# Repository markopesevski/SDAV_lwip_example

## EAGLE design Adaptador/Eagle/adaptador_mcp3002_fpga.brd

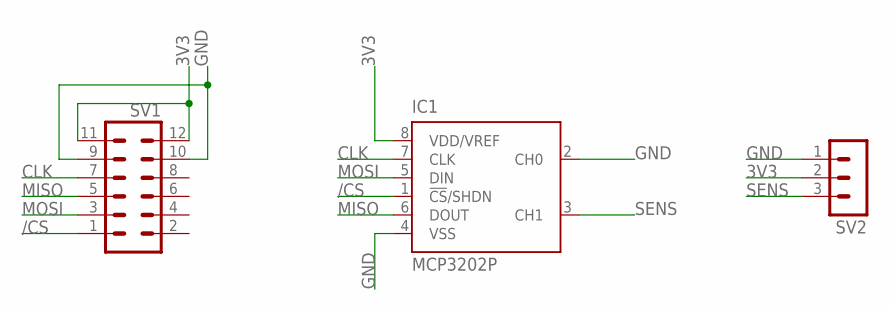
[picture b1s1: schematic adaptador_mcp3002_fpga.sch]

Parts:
IC1: MCP3202P; DIL8
SV1: MA06-2
SV2: MA03-1

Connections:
3V3: IC1.8 (VDD/VREF), SV1.11, SV1.12, SV2.2
/CS: IC1.1 (!CS!/SHDN), SV1.1
CLK: IC1.7 (CLK), SV1.7
GND: IC1.2 (CH0), IC1.4 (VSS), SV1.9, SV1.10, SV2.1
MISO: IC1.6 (DOUT), SV1.5
MOSI: IC1.5 (DIN), SV1.3
SENS: IC1.3 (CH1), SV2.3

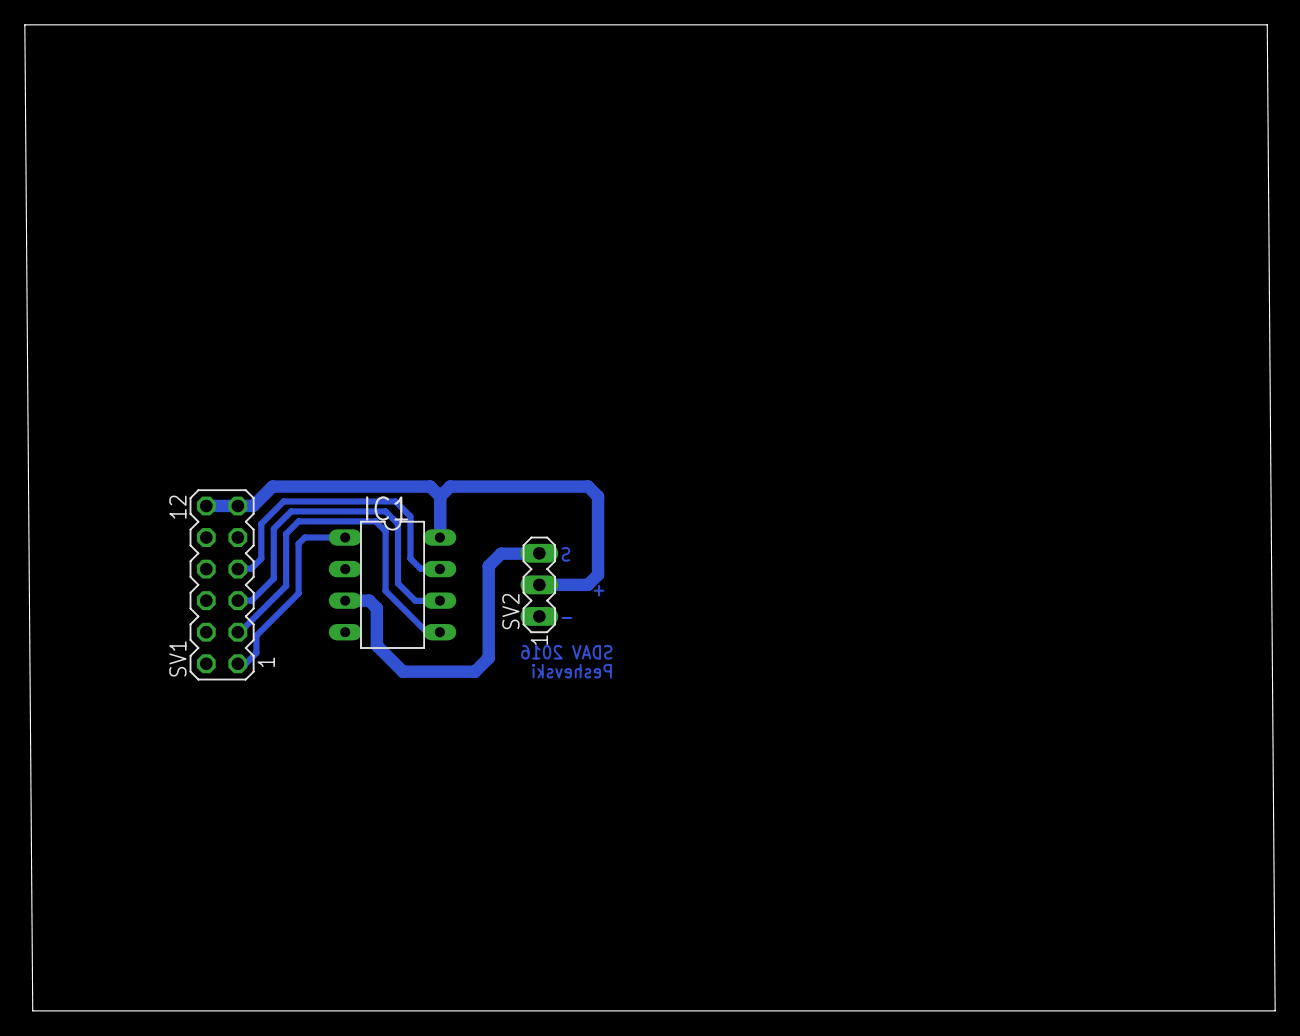
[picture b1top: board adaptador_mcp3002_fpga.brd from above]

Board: 2 copper layers, 100.6 x 79.4 mm, 3 parts (0 on the bottom side), 7 nets.

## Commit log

2016-10-20 Commit inicial de l'exemple de LWIP de Xilinx, sense haver fet cap modificacio
2016-10-20 Afegit README.md
2016-10-24 Primer canvi cap a la web propia
2016-10-24 Segon canvi, segueix reiniciant-se per raons desconegudes (carrega el programa be a la FPGA)
2016-10-24 Alguns canvis a l'estructura de dintre de la pagina web, ara compilara al mfs tot el que hi ha dintre de la carpeta WEB/webpage
2016-10-24 Deixar de seguir molts arxius inutils
2016-10-24 Alguns canvis rellevants sobretot al .bat. Per altra banda segueix fent resets continus a l'hora de posar en marxa les interrupts
2016-10-24 Proves per intentar que funcionin les interrupts i no faci resets
2016-10-24 Al commit anterior hi faltava aquest canvi
2016-10-25 Canvis chorra que no han ajudat a res
2016-10-25 Afegides algunes chorradetes i algun canvi important al .bat, ara genero el bitstream de bootloop cada cop que intento carregar la app a la FPGA
2016-10-26 Proves varies pero totes infructuoses
2016-11-12 Primera versio "mes o menys 'funcional'" a app2
    El que he fet ha sigut copiar el codi trosset per trosset de l'altra app (raw_apps) i d'aquesta manera ha acabat no petant. De moment he eliminat la part de DHCP del main, que directament demani al r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
2016-11-12 Canvis minims al gitignore
2016-11-13 Dono mes memoria de stack i heap (tot i que crec que no es necessari)
2016-11-13 Canvi tonto per no confondre i apuntar a llocs que no son
2016-11-13 Afegit DHCP al codi (s'havia tret abans, pero no fa cap mal que hi sigui, al contrari, millor)
2016-11-13 La solucio per la qual no funcionava fins ara, si no s'inicialitza LwIP evidentment no funcionara
2016-11-13 Canvis al gitignore per no ignorar el que passa a dintre de WEB
2016-11-13 Canvis tontos a la web per comprovar que funciona (efectivament ho fa) + afegit script de shell per crear el mfs a Linux
2016-11-15 Primera enorme neteja del codi. Eliminats molts arxius, reestructurat el codi i borrats molts comentaris inutils
2016-11-15 Continuo amb la neteja anterior, i encara no he acabat
2016-11-15 Canvis en chorrades de missatges de consola i similars
2016-11-15 Mes petites neteges del codi
2016-11-15 Començo a fer debug de les coses per entendre com funciona una mica
2016-11-15 Afegeixo coses al HTML tal com ho trobo d'aqui: https://blog.idrsolutions.com/2013/12/websockets-an-introduction/
2016-11-16 Primera versio integrant algo de websockets, per encaminar-ho be
2016-11-16 Rebo la peticio de crear un nou WS pero a l'hora d'elevar el protocol no soc capaç de generar la clau que necessita el navegador. Pagina per la informacio sobre WS: https://tools.ietf.org/html/rfc645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
2016-11-16 Commit per mostrar be el resultat del hash SHA1. ES CORRECTE, comprovat amb https://emn178.github.io/online-tools/sha1.html. Per aquesta key 'tJT/dU+OHMGaBP5cUW2DUQ==258EAFA5-E914-47DA-95CA-C5AB0DC85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
2016-11-16 Sembla que el WS esta a punt per ser obert pero per alguna rao no l'obre. Crec que es la codificacio de base64 que fa que tot vagi malament, pero no estic segur
2016-11-16 Sembla ser que en realitat el protocol ja esta obert. Ara cal desxifrar els missatges. Un bon lloc per seguir sembla ser: https://blog.pusher.com/websockets-from-scratch/
2016-11-16 Efectivament el socket es pot obrir i es poden enviar missatges. Ara cal parsejar-ho i provar de fer l'altre sentit (MicroBlaze -> Client)
2016-11-16 Interpreta correctament les dades enviades a traves del websocket en la direccio client -> servidor (desenmascarar). Ara falta la comunicacio al contrari
2016-11-16 Ja puc enviar servidor -> client. La comunicacio es ben senzilla quan fas servir paquets de <=127 bytes de longitud
2016-11-16 Prova de fer funcionar el sensor a l'Arduino, dona uns valors d'uns 620-720 ticks del ADC de l'Arduino, alimentant-lo a 5V
2016-11-17 Importat el codi per llegir el MCP3002 per SPI. De moment hi ha problemes amb enviar les dades cada x ms perque no se sap quin es el tcp_pcb que s'ha de fer servir per enviar les dades
2016-11-17 La comunicacio per timers (al menys amb els timers de la llibreria LWIP, tcp_fasttmr i tcp_slowtmr) no sembla possible o facil. Aixi que el que es pot fer (i el que es fa de moment) es demanar dades 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
2016-11-17 Per fi puc fer la puta transmissio per temps. Faltava calcular be la longitud del payload (el numero a enviar)
2016-11-17 Canvis en el SPI, començo a enviar algunes dades amb sentit (de moment el valor cru del ADC)
2016-11-18 Canvio missatges que mostro a la consola de la FPGA per no saturar i començo a fer canvis a la web per representar les dades
2016-11-18 Primera versio 'funcional' de la web, mostra les dades correctament pero amb punts petitets de moment
2016-11-18 Elimino d'aqui l'enviament de dades, pero deixo el desxifrar el missatge perque pot ser que calgui fer calibracio
2016-11-18 Canviat color i tamany dels punts del grafic a la web
2016-11-18 Afegida placa adaptadora per no necessitar la breadboard. ES POSSIBLE QUE TOT ESTIGUI AL REVES. Estic massa cansat per pensar
2016-11-18 Canvis a la PCB. No puc dormir sino. Crec que ara esta be (el coure queda a la vista cap a dalt i tot es munta per baix
2016-11-18 Afegida impressio amb els 4 mirrors a veure quin es al final
2016-11-23 Afegit timer per enviar les dades molt rapid (3 vegades mes rapid que TcpFastTmr), i canvi a la web per mostrar una grafica amb l'eix Y limitat [0, 1023]. A mes ara mostra les 20 ultimes mostres
2016-11-23 Eliminats alguns camps de la web
2016-11-23 Afegida PCB feta amb Eagle
2016-11-23 Primer commit del document, ja s'ha escrit bastant per aixo
2016-11-24 Deixo de seguir aquests arxius que no serveixen per res
2016-11-24 Canvis al gitignore per deixar de seguir alguns dels arxius del document LaTeX, i canvis al document
2016-11-24 Canvis en el document
2016-11-24 Petit canvi a la web per eliminar el boto que s'havia posat de 'Close socket'. Sera mes lio que una altra cosa implementar que es puguin tancar WebSockets
2016-11-24 Canvis al document, afegida captura de la web, conclusions i treball futur. En principi 'acabat'
2016-11-24 Afegida impressio de la placa adaptaora feta amb Eagle. Sembla que el espai entre el poligon de massa i els pads es massa poc
2016-11-24 Eliminat aquest arxiu inutil que donava errors estupids
2016-11-25 Primera versio del poster
2016-11-28 Canviada la placa feta amb Eagle, ara els components estan com toca
2016-11-29 Canvis al poster: marges, canviades fletxes, canviada la foto del router (ara es una foto d'un real)
2016-12-01 Afegida presentacio amb totes les figures
2016-12-01 Afegides algunes diapositives: les intermitges per dir que cada ? passa a ser conegut i la de la estructura del software del servidor
2016-12-01 Afegida frase a la diapositiva de la FPGA - xarxa
